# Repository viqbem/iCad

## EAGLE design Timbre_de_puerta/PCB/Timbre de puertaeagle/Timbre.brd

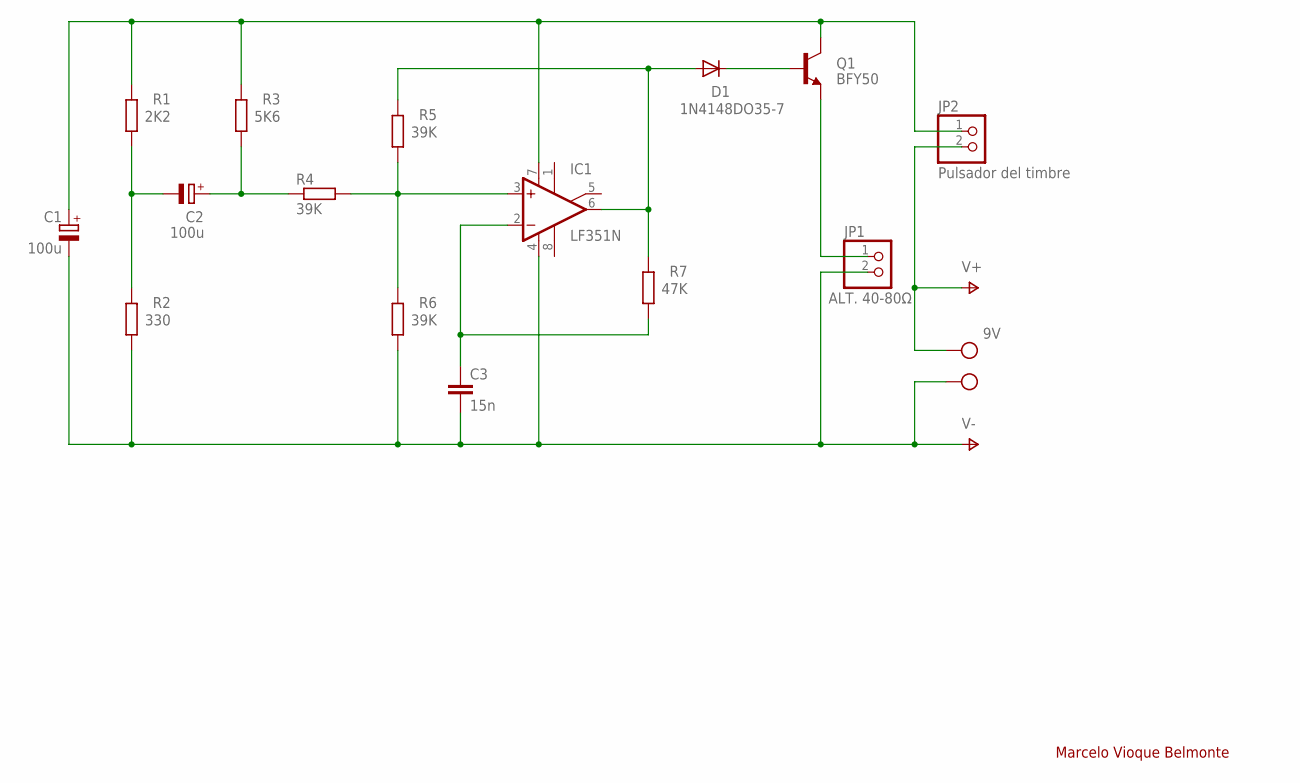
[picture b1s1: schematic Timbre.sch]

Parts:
C1, C2: 100u; E2,5-6
C3: 15n; C025_050-025X075
D1: 1N4148DO35-7; DO35-7
IC1: LF351N; DIL08
JP1: ALT. 40-80Ω; 1X02
JP2: Pulsador del timbre; 1X02
Q1: BFY50; TO39
R1: 2K2; 0207/10
R2: 330; 0207/10
R3: 5K6; 0207/10
R4, R5, R6: 39K; 0207/10
R7: 47K; 0207/10
X1: 9V; AK500/2

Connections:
unnamed: IC1.3 (+IN), R4.2, R5.1, R6.2
unnamed: D1.A, IC1.6 (OUT), R5.2, R7.2
unnamed: C3.1, IC1.2 (-IN), R7.1
unnamed: D1.C, Q1.2 (B)
unnamed: C2.+, R3.1, R4.1
unnamed: C1.+, IC1.7 (V+), JP2.1, Q1.3 (C), R1.2, R3.2
unnamed: C2.-, R1.1, R2.2
unnamed: JP1.1, Q1.1 (E)
V+: JP2.2, X1.2
V-: C1.-, C3.2, IC1.4 (V-), JP1.2, R2.1, R6.1, X1.1

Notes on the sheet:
Marcelo Vioque Belmonte

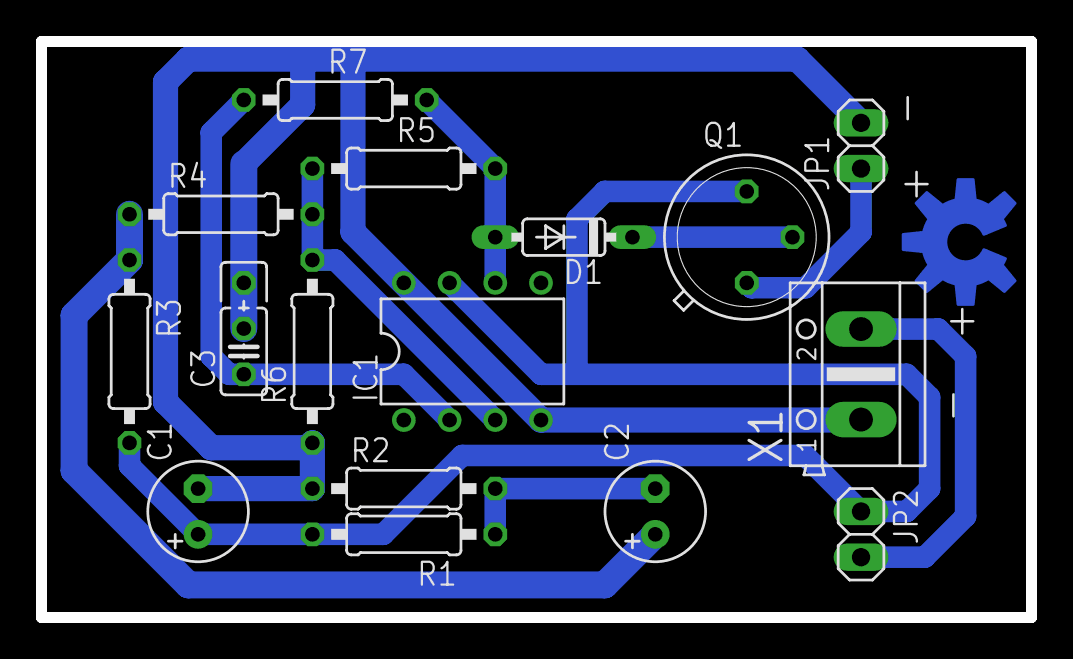
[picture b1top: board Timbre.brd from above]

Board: 2 copper layers, 55.0 x 32.0 mm, 17 parts (0 on the bottom side), 10 nets.

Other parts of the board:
U$1: OSHW-LOGO-L

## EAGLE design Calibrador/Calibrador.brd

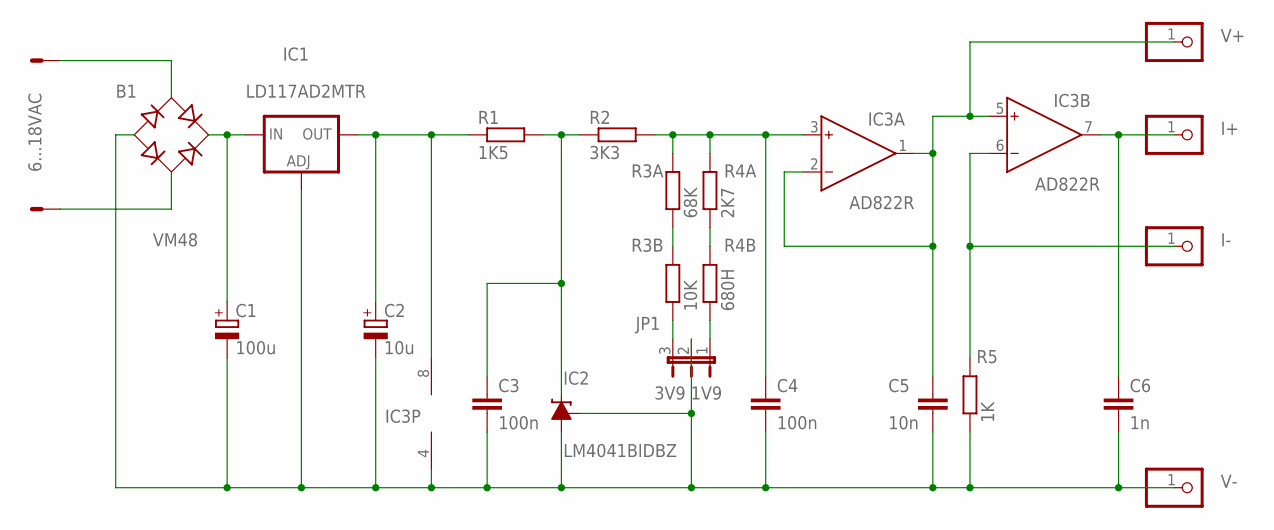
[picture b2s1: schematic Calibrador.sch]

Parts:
B1: VM48; B-DIL
C1: 100u; 153CLV-0807
C2: 10u; 153CLV-0505
C3, C4: 100n; C0805
C5: 10n; C0805
C6: 1n; C0805
IC1: LD117AD2MTR; D2PACK
IC2: LM4041BIDBZ; DBZ_R-PDSO-G3
IC3: AD822R; SO8
J1: 22-27-2021-02; 6410-02
JP1: 3V9 1V9; JP2
JP2: V+; 1X01
JP3: I+; 1X01
JP4: I-; 1X01
JP5: V-; 1X01
R1: 1K5; 0207/10
R2: 3K3; 0207/10
R3A: 68K; 0207/10
R3B: 10K; 0207/10
R4A: 2K7; 0207/10
R4B: 680H; 0207/10
R5: 1K; 0207/10

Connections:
unnamed: B1.AC1, J1.2
unnamed: B1.AC2, J1.1
unnamed: C3.1, IC2.2 (C), R1.2, R2.1
unnamed: B1.+, C1.+, IC1.3 (IN)
unnamed: C2.+, IC1.2 (OUT), IC3.8 (V+), R1.1
unnamed: B1.-, C1.-, C2.-, C3.2, C4.2, C5.2, C6.2, IC1.1 (ADJ), IC2.1 (FB), IC2.3 (A), IC3.4 (V-), JP1.2, JP5.1, R5.1
unnamed: JP1.3, R3B.1
unnamed: JP1.1, R4B.1
unnamed: R4A.1, R4B.2
unnamed: R3A.1, R3B.2
unnamed: C4.1, IC3.3 (IN+), R2.2, R3A.2, R4A.2
unnamed: C5.1, IC3.1 (OUT), IC3.2 (IN-), IC3.5 (IN+), JP2.1
unnamed: C6.1, IC3.7 (OUT), JP3.1
unnamed: IC3.6 (IN-), JP4.1, R5.2

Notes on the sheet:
6...18VAC

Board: 2 copper layers, 23 parts (0 on the bottom side), 14 nets, no tracks yet.

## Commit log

2015-08-10 Create Calibrador
2015-08-10 archivos Eagle
2015-08-11 Hembrilla seguridad HBS
2015-08-13 Goma pasacables
2016-05-15 elimino archivos innecesarios
2016-05-15 Protection for outdoor wireless doorbell
2016-06-19 i add parts list
2016-06-19 I add exploded assembly
2016-08-28 I add proposed projec
2016-09-04 agrego archivos
2016-09-04 Dispositivo RGB para K8200
2016-09-10 manufacturing files
2017-04-01 Accesorio domo
2017-04-01 elimino archivos
2017-04-01 Electric connect
2017-04-08 actualización
2017-04-17 modifico archivos
2017-04-29 añado x2 carpetas nuevas
2017-04-29 Thermostat XH-W1411
2017-04-29 agrego archivos nuevos
2017-08-25 agrego carpeta
2017-08-28 arreglos
2017-08-28 elimino archivor innecesarios
2017-10-16 archivos modificados
2017-10-17 agrego archivos .nc
2018-11-25 Add files via upload
    Agrego imagen
2019-09-12 kit de reloj
2019-09-12 Sistema iluminación eco

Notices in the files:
parts and their libraries:
SparkFun-Aesthetics: Licensing: Creative Commons ShareAlike 4.0 International - https://creativecommons.org/licenses/by-sa/4.0
